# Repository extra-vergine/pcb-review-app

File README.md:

# PCB Review

A personal macOS app (Swift/SwiftUI) for reviewing KiCad 10 board files.

Planned:
1. KiCad 10 `.kicad_pcb` / `.kicad_pro` / `.kicad_dru` reader
2. Board view with layer toggles
3. Deterministic DRC and JLCPCB / PCBWay fab-rule checks with clickable findings
4. Separately labelled AI review

## Layout

- `Sources/KiCadKit`: the reader library (no UI). Parses `.kicad_pcb`, `.kicad_pro` and `.kicad_dru` into a board model in absolute millimetre coordinates.
- `Sources/kicad-inspect`: a small command line tool that prints a summary of a board.
- `Sources/PCBReview`: the SwiftUI macOS app (board view, layers, inspector). Built only on macOS.
- `Tests/KiCadKitTests`: tests against the THRH_Node (Roomy v4) sample board.

```sh
swift test
swift run kicad-inspect Tests/KiCadKitTests/Fixtures/THRH_Node.kicad_pcb
```

## Running the app (macOS)

```sh
swift run PCBReview Tests/KiCadKitTests/Fixtures/THRH_Node.kicad_pcb
```

Or open `Package.swift` in Xcode and run the `PCBReview` scheme, then use File › Open Board (⌘O).

Navigation: pinch, ⌘-scroll, ⌘+ (also ⌘ numpad + or ⌘⇧1) / ⌘− to zoom (a mouse wheel zooms directly), two-finger scroll, drag or the arrow keys to pan (Shift moves further), ⌘0 to fit, click to select, Esc to clear the selection.

- Tabs above the board: All active layers, then each copper layer (⌘1, ⌘2, …).
- Layers: green check marks switch layers on and off; click a colour swatch to change its colour (right-click to reset).
- View: rulers (⌘R, click a ruler to cycle mm → in → pt → mil, drag from a ruler to place a guide, drag a guide back onto its ruler to remove it, View › Clear All Guides), origin marker (click it to step the origin: file origin, lower left, lower right, centre, upper right, upper left, back to the file origin), Flip X (⇧⌘X) and Flip Y (⇧⌘Y).
- Dimensions on User.Drawings: overall board size and mounting-hole spacing.
- Left panel: a viewfinder (drag the frame to move the view, double-click for zoom to fit and the default layers), and menus for the origin, the board material and the solder mask colour (the file's, or what JLCPCB and PCBWay offer).
- 2D / 3D switch above the board. In 3D the viewfinder becomes a view cube: click a face to look from that side, the house returns to the home view, the eye switches between perspective and orthographic.
- File: Page Setup (⇧⌘P), Print (⌘P), and Export to PDF (true scale), PNG, SVG, HP-GL, GLB and USDZ.

## Design checks

The Findings panel (right side) runs deterministic checks when a board opens, in two clearly separate sections:

- **KiCad rules**: the board's own rules from the `.kicad_pro` (board setup minimums, net class clearances) and the `.kicad_dru` (custom rules, with the last matching rule winning as in KiCad). A custom rule whose condition uses something the checker does not understand is listed under "Rules not checked" instead of being guessed.
- **Fab limits**: JLCPCB or PCBWay, picked at the top of the panel. Each limit lives in a data file in `Sources/KiCadKit/Profiles/` with the fab's page, the wording on it and the date it was checked. Values not confirmed word for word give warnings, not errors, and so do silkscreen limits.

Checked: copper clearance (tracks, pads, vias, zone fills), hole to copper, hole to hole, copper to board edge, track width, via size, drill and annular ring, pad drill, slot width and annular ring, silkscreen line width and clearance to pads, text height and thickness, board thickness. Not checked yet: connectivity (unrouted nets), zone fill rules, courtyards and solder mask. Use KiCad's own DRC for those.

- **KiCad DRC cross-check**: the "Cross-check with KiCad DRC" button runs `kicad-cli pcb drc` (from KiCad in /Applications) on the same file and lists its violations, unconnected items and parity problems in a third section, so the two can be compared.

Click a finding to zoom to it. Checks › Next / Previous Finding (⌘] / ⌘[), Run Checks Again (⇧⌘K), Copy Findings as Text (⇧⌘C).

```sh
swift run kicad-inspect board.kicad_pcb --check jlcpcb   # or pcbway, or kicad
```

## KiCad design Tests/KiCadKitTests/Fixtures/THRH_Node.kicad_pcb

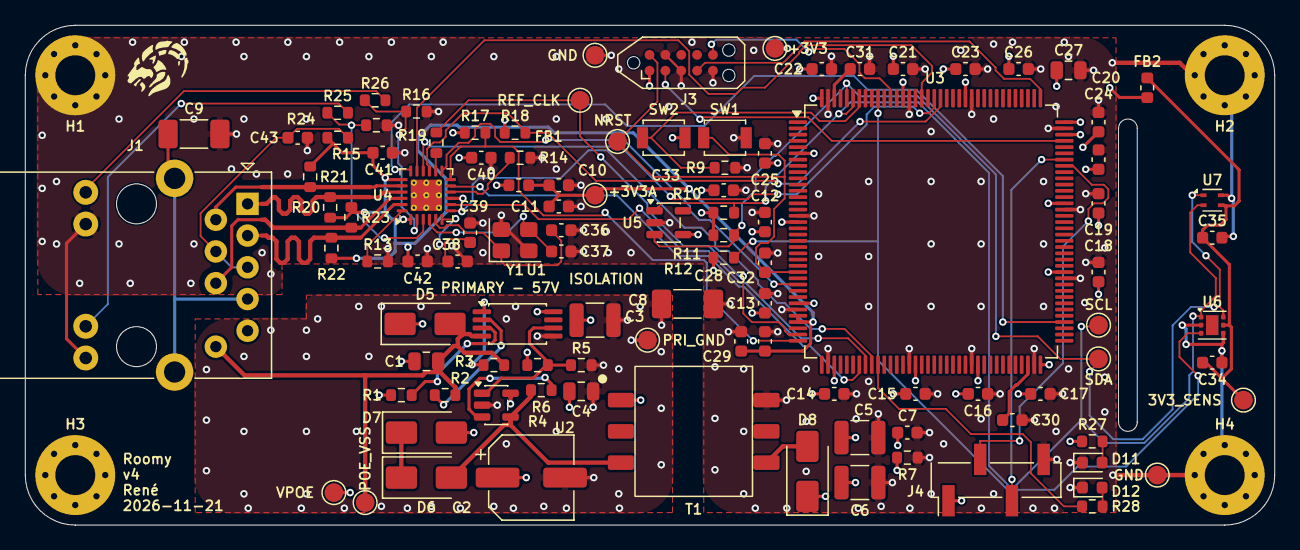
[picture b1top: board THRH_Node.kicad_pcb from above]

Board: 4 copper layers, 100.0 x 40.0 mm, 108 parts (0 on the bottom side), 56 nets.

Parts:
C1, C4: 100n/100V; C_0805_2012Metric
C2: 22u/100V; CP_Elec_6.3x7.7
C3: 2.2u/100V; C_1210_3225Metric
C5, C6: 47u/6.3V; C_1210_3225Metric
C7, C11, C12, C13, C14, C15, C16, C17, C18, C19, C20, C21, C22, C23, C24, C25, C29, C32, C33, C34, C35, C40, C41, C42, C43: 100n; C_0603_1608Metric
C8: 1n/3kV Y; C_1808_4520Metric
C9: 1n/3kV; C_1808_4520Metric
C10, C26: 4.7u; C_0603_1608Metric
C27: 10u; C_0805_2012Metric
C28, C38: 1u; C_0603_1608Metric
C30, C31: 2.2u; C_0603_1608Metric
C36, C37: 18p; C_0603_1608Metric
C39: 470p; C_0603_1608Metric
D5: SMAJ58A; D_SMA
D6: ES1J; D_SMA
D7: SMAJ36A; D_SMA
D8: SS34; D_SMA
D11: green PWR; LED_0603_1608Metric
D12: blue STAT; LED_0603_1608Metric
FB1, FB2: 600R@100MHz; L_0603_1608Metric
H1, H2, H3, H4: M3; MountingHole_3.2mm_M3_Pad_Via
J1: ARJP11A-MASA-B-A-EMU2; RJ45_Abracon_ARJP11A-MA_Horizontal
J3: SWD Tag-Connect; Tag-Connect_TC2050-IDC-NL_2x05_P1.27mm_Vertical
J4: UART + 3V3 bench in; PinHeader_1x04_P2.54mm_Vertical_SMD_Pin1Left
R1: 24.9k 1%; R_0603_1608Metric
R2: 953 1%; R_0603_1608Metric
R3: 178k 1%; R_0603_1608Metric
R4: 1M 1%; R_0603_1608Metric
R5: 34.8k 1%; R_0603_1608Metric
R6: 294k 1%; R_0603_1608Metric
R7, R28: 1k; R_0603_1608Metric
R9, R12, R14, R15, R16, R18: 10k; R_0603_1608Metric
R10, R11, R27: 2.2k; R_0603_1608Metric
R13: 12.1k 1%; R_0603_1608Metric
R17: 1.5k; R_0603_1608Metric
R19: 33; R_0603_1608Metric
R20, R21, R22, R23: 49.9 1%; R_0603_1608Metric
R24: 0; R_0603_1608Metric
R25, R26: 470; R_0603_1608Metric
SW1: RESET; SW_SPST_B3U-1000P
SW2: BOOT; SW_SPST_B3U-1000P
T1: 750315825; Wurth_WE-FLYLT_EP7_750315825
TP1: VPOE; TestPoint_Pad_D1.5mm
TP2: PRI_GND; TestPoint_Pad_D1.5mm
TP3: +3V3; TestPoint_Pad_D1.5mm
TP4, TP10: GND; TestPoint_Pad_D1.5mm
TP5: +3V3A; TestPoint_Pad_D1.5mm
TP6: I2C_SCL; TestPoint_Pad_D1.5mm
TP7: I2C_SDA; TestPoint_Pad_D1.5mm
TP8: ETH_REF_CLK; TestPoint_Pad_D1.5mm
TP9: NRST; TestPoint_Pad_D1.5mm
TP11: +3V3_SENS; TestPoint_Pad_D1.5mm
TP12: POE_VSS; TestPoint_Pad_D1.5mm
U1: TPS2375PW-1; TSSOP-8_4.4x3mm_P0.65mm
U2: LT8303ES5; TSOT-23-5
U3: STM32H563ZIT6; LQFP-144_20x20mm_P0.5mm
U4: LAN8742A-CZ; VQFN-24-1EP_4x4mm_P0.5mm_EP2.5x2.5mm_ThermalVias
U5: 24AA02E48T-I/OT; SOT-23-5
U6: TMP117AIDRVR; WSON-6-1EP_2x2mm_P0.65mm_EP1x1.6mm
U7: SHT45-AD1B; Sensirion_DFN-4_1.5x1.5mm_P0.8mm_SHT4x_NoCentralPad
Y1: 25MHz CL12pF; Crystal_SMD_3225-4Pin_3.2x2.5mm

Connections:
+3V3: C5.1, C6.1, C7.1, C12.1, C13.1, C14.1, C15.1, C16.1, C17.1, C18.1, C19.1, C20.1, C21.1, C22.1, C23.1, C24.1, C25.1, C26.1, C27.1, C33.1, C40.1, D8.1, FB1.1, FB2.1, J3.1, J4.1, R7.1, R10.1, R11.1, R12.1, R17.1, R18.1, R27.1, SW2.2, TP3.1, U3.6, U3.17, U3.30, U3.39, U3.52, U3.62, U3.72, U3.84, U3.95, U3.106, U3.108, U3.121, U3.131, U3.144, U4.9, U5.4
+3V3A: C10.1, C11.1, C28.1, C29.1, C41.1, C42.1, FB1.2, R20.1, R21.1, R22.1, R23.1, R24.1, TP5.1, U3.32, U3.33, U4.1, U4.19
+3V3_SENS: C34.1, C35.1, FB2.2, TP11.1, U6.5, U7.3
/Debug & indicators/D11_A: D11.2, R27.2
/Debug & indicators/D12_A: D12.2, R28.2
/Ethernet/CHASSIS: C9.1, J1.7, J1.SH
/Ethernet/ETH_CT: C43.1, J1.4, J1.5, R24.2
/Ethernet/ETH_RXN: J1.6, R23.2, U4.22
/Ethernet/ETH_RXP: J1.3, R22.2, U4.23
/Ethernet/ETH_TXN: J1.2, R21.2, U4.20
/Ethernet/ETH_TXP: J1.1, R20.2, U4.21
/Ethernet/LED_LINK_A: J1.13, R25.2
/Ethernet/LED_SPEED_A: J1.11, R26.2
/Ethernet/PHY_LED1: R15.1, R25.1, U4.3
/Ethernet/PHY_LED2: R16.1, R26.1, U4.2
/Ethernet/PHY_RBIAS: R13.1, U4.24
/Ethernet/PHY_REFCLKO: R19.1, U4.14
/Ethernet/PHY_RXER: R14.1, U4.10
/Ethernet/PHY_VDDCR: C38.1, C39.1, U4.6
/Ethernet/PHY_XI: C36.1, U4.5, Y1.1
/Ethernet/PHY_XO: C37.1, U4.4, Y1.3
/Microcontroller/BOOT0: R9.1, SW2.1, U3.138
/Microcontroller/VCAP1: C30.1, U3.70
/Microcontroller/VCAP2: C31.1, U3.142
/Power/POE_CLASS: R2.1, U1.2
/Power/POE_DET: R1.2, U1.3
/Power/POE_ILIM: R3.1, U1.1
/Power/PRI_CLAMP: D6.1, D7.1
/Power/PRI_GND: C2.2, C3.2, C4.2, C8.1, R5.2, TP2.1, U1.5, U2.2
/Power/PRI_RFB: R6.2, U2.3
/Power/PRI_SW: D6.2, R6.1, T1.3, U2.4
/Power/PSU_EN: R4.2, R5.1, U1.6, U2.1
/Power/SEC_SW: D8.2, T1.4
ETH_CRS_DV: U3.43, U4.11
ETH_MDC: U3.27, U4.13
ETH_MDIO: R17.2, U3.36, U4.12
ETH_NRST: R18.2, U3.125, U4.15
ETH_REF_CLK: R19.2, TP8.1, U3.35
ETH_RXD0: U3.44, U4.8
ETH_RXD1: U3.45, U4.7
ETH_TXD0: U3.128, U4.17
ETH_TXD1: U3.76, U4.18
ETH_TX_EN: U3.126, U4.16
GND: C5.2, C6.2, C7.2, C8.2, C9.2, C10.2, C11.2, C12.2, C13.2, C14.2, C15.2, C16.2, C17.2, C18.2, C19.2, C20.2, C21.2, C22.2, C23.2, C24.2, C25.2, C26.2, C27.2, C28.2, C29.2, C30.2, C31.2, C32.2, C33.2, C34.2, C35.2, C36.2, C37.2, C38.2, C39.2, C40.2, C41.2, C42.2, C43.2, D11.1, D12.1, H1.1, H2.1, H4.1, J1.12, J1.14, J3.3, J3.5, J3.9, J4.4, R7.2, R9.2, R13.2, R14.2, R15.2, R16.2, SW1.2, T1.6, TP4.1, TP10.1, U3.16, U3.31, U3.38, U3.51, U3.61, U3.71, U3.83, U3.94, U3.107, U3.120, U3.130, U3.143, U4.25, U5.2, U6.2, U6.4, U7.4, Y1.2, Y1.4
I2C_SCL: R10.2, TP6.1, U3.139, U5.1, U6.1, U7.2
I2C_SDA: R11.2, TP7.1, U3.140, U5.3, U6.6, U7.1
LED_STAT: R28.1, U3.46
NRST: C32.1, J3.10, SW1.1, TP9.1, U3.25
POE_VSS: C1.2, D5.2, J1.10, R2.2, R3.2, TP12.1, U1.4
SWCLK: J3.4, U3.109
SWDIO: J3.2, U3.105
SWO: J3.6, U3.133
TMP_ALERT: R12.2, U3.135, U6.3
UART_RX: J4.3, U3.102
UART_TX: J4.2, U3.101
VPOE: C1.1, C2.1, C3.1, C4.1, D5.1, D7.2, J1.9, R1.1, R4.1, T1.1, TP1.1, U1.8, U2.5
